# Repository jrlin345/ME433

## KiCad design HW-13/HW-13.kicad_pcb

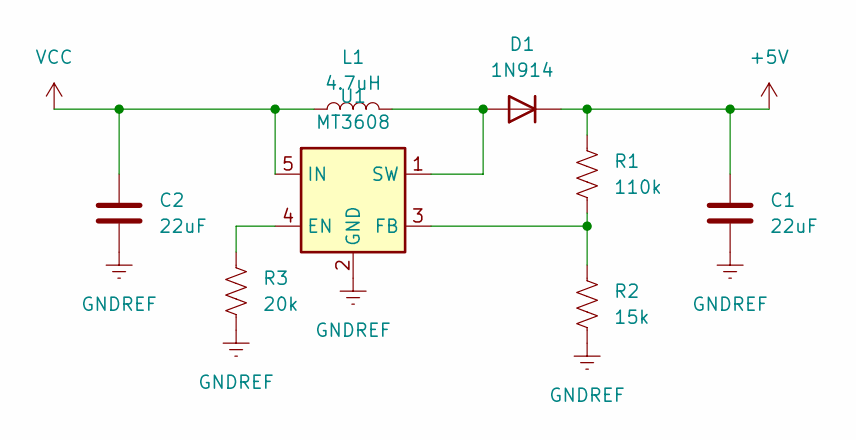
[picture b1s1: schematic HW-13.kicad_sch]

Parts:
C1, C2: 22uF; C_0805_2012Metric
D1: 1N914; D_DO-35_SOD27_P7.62mm_Horizontal
L1: 4.7uH; L_01005_0402Metric
R1: 110k; R_0805_2012Metric
R2: 15k; R_0805_2012Metric
R3: 20k; R_0805_2012Metric
U1: MT3608; SOT-23-6

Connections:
+5V: C1.1, D1.1 (K), R1.1
GNDREF: C1.2, C2.2, R2.2, R3.2, U1.2 (GND)
unnamed: D1.2 (A), L1.2, U1.1 (SW)
unnamed: R3.1, U1.4 (EN)
unnamed: R1.2, R2.1, U1.3 (FB)
VCC: C2.1, L1.1, U1.5 (IN)

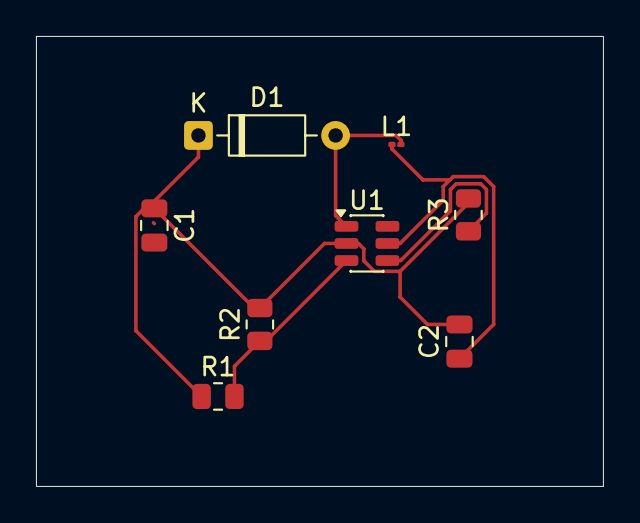
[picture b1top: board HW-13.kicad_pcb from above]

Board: 2 copper layers, 31.5 x 25.0 mm, 8 parts (0 on the bottom side), 6 nets.

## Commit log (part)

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2026-04-03 HW-2
2026-04-30 HW-9
2026-05-02 HW-10
2026-05-07 HW11
2026-05-21 CANandForceSensing
2026-06-02 Hw-16
2026-06-08 Hw-17
2026-06-09 Final Project
